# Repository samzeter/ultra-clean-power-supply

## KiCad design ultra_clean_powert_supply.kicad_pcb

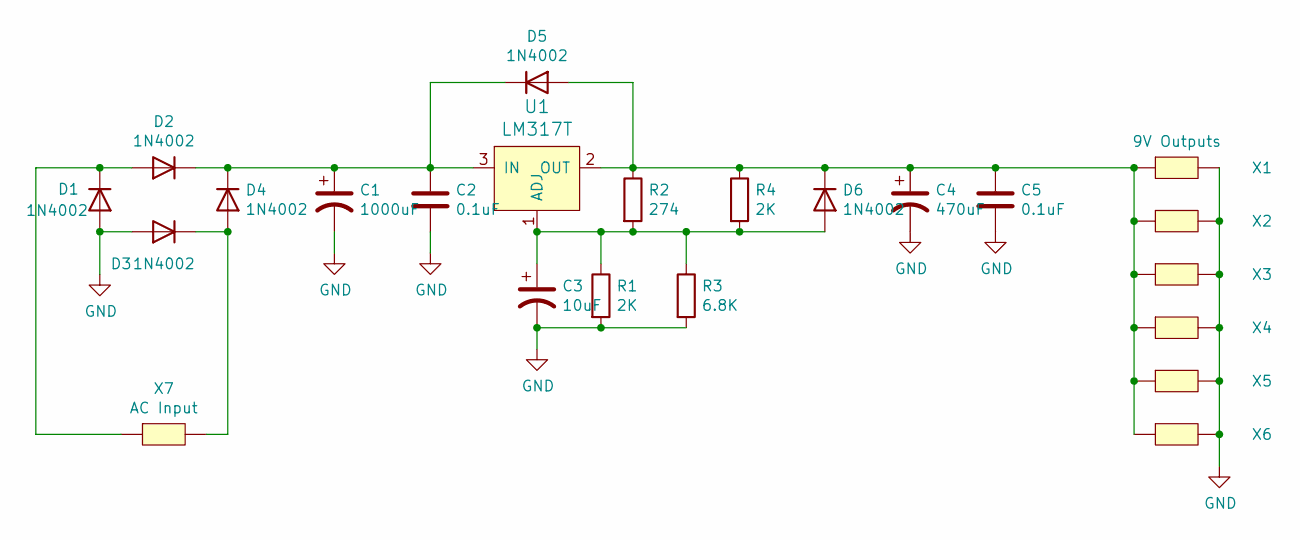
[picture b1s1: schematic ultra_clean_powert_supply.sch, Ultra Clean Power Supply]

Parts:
C1: 1000uF; CP_Radial_D16.0mm_P7.50mm
C2, C5: 0.1uF; C_Rect_L9.0mm_W3.8mm_P7.50mm_MKT
C3: 10uF; CP_Radial_D8.0mm_P5.00mm
C4: 470uF; CP_Radial_D10.0mm_P7.50mm
D1, D2, D3, D4, D5, D6: 1N4002; D_DO-41_SOD81_P10.16mm_Horizontal
R1, R4: 2K; R_Axial_DIN0207_L6.3mm_D2.5mm_P10.16mm_Horizontal
R2: 274; R_Axial_DIN0207_L6.3mm_D2.5mm_P10.16mm_Horizontal
R3: 6.8K; R_Axial_DIN0207_L6.3mm_D2.5mm_P10.16mm_Horizontal
U1: LM317T; TO-220-3_Vertical; MPN LM317T; Digi-Key_PN 497-1575-5-ND
X1: 9V Outputs; dual_pads
X2, X3, X4, X5, X6: Dualpads; dual_pads
X7: AC Input; dual_pads

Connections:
GND: C1.2, C2.2, C3.2, C4.2, C5.2, D1.2 (A), D3.2 (A), R1.2, R3.2, X1.2, X2.2, X3.2, X4.2, X5.2, X6.2
unnamed: C1.1, C2.1, D2.1 (K), D4.1 (K), D5.1 (K), U1.3 (IN)
unnamed: C3.1, D6.2 (A), R1.1, R2.2, R3.1, R4.2, U1.1 (ADJ)
unnamed: C4.1, C5.1, D5.2 (A), D6.1 (K), R2.1, R4.1, U1.2 (OUT), X1.1, X2.1, X3.1, X4.1, X5.1, X6.1
unnamed: D1.1 (K), D2.2 (A), X7.1
unnamed: D3.1 (K), D4.2 (A), X7.2

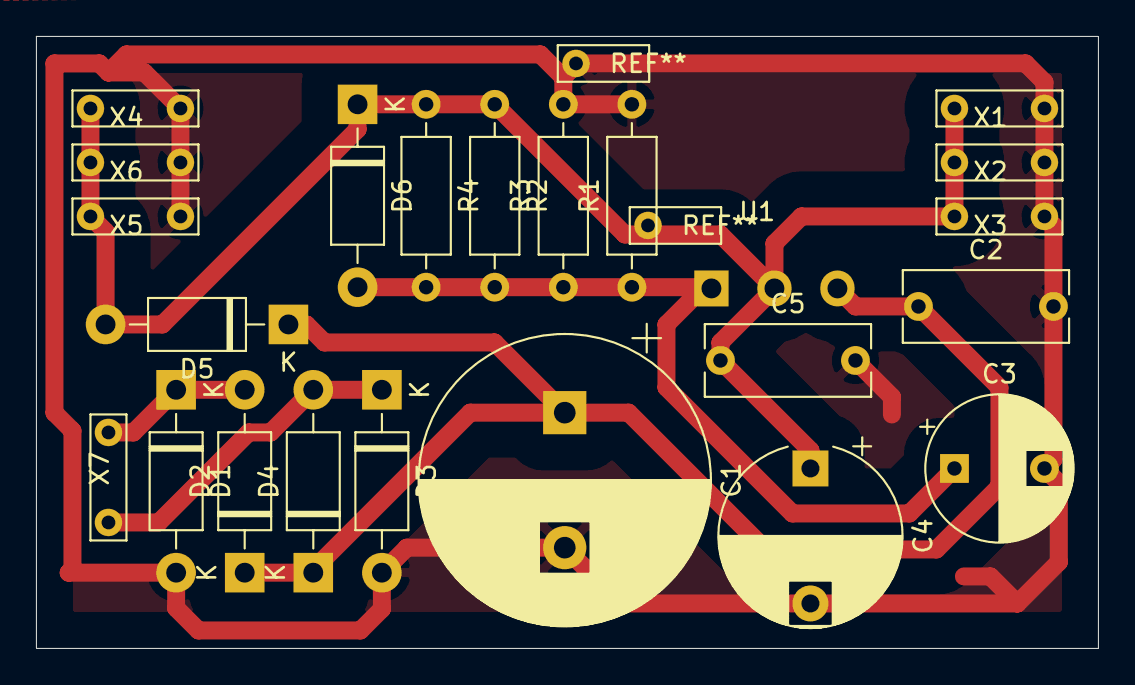
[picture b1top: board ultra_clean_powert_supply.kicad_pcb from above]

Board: 2 copper layers, 59.0 x 34.0 mm, 23 parts (0 on the bottom side), 6 nets.
